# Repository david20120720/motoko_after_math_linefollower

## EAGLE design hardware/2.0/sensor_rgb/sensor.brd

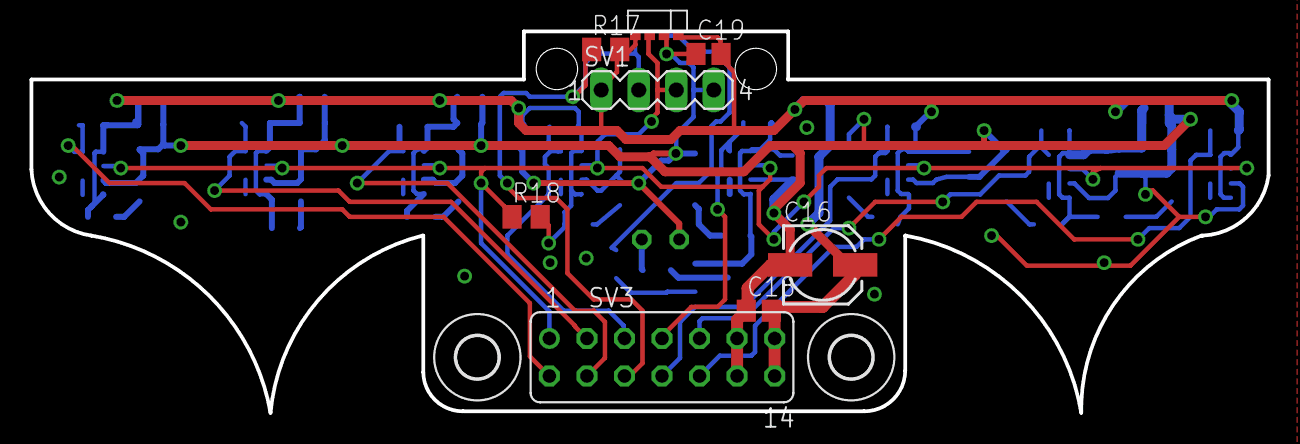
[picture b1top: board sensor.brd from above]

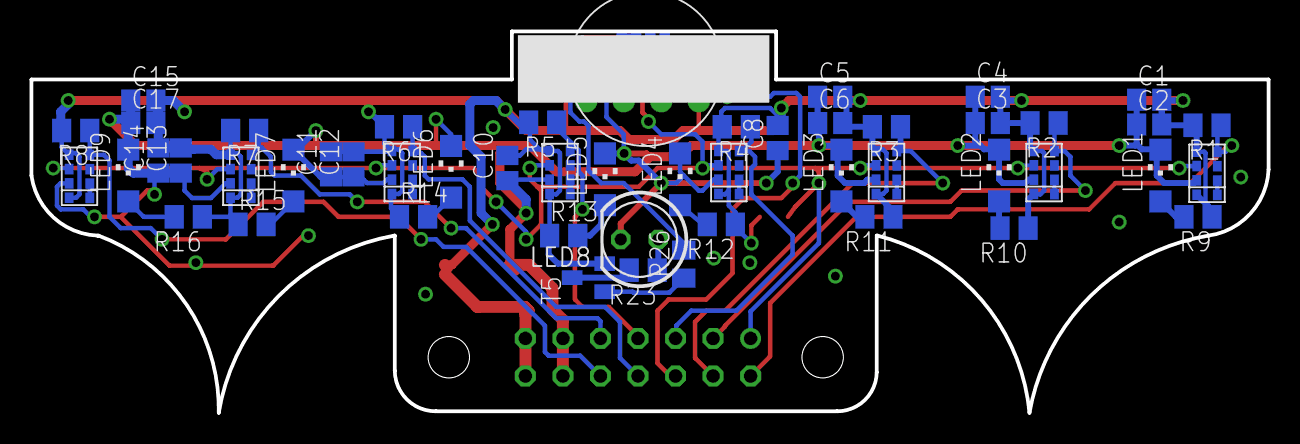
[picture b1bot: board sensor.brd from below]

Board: 2 copper layers, 83.7 x 25.8 mm, 61 parts (51 on the bottom side), 32 nets.

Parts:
C1, C3, C5, C11, C13, C15, C18: 10uF; C0805
C2, C4, C6, C8, C10, C12, C14, C17, C19: 100n; C0805
C16: 22uF; 153CLV-0505
H3, H4: MOUNT-HOLE2.8; 2,8
LED1, LED2, LED3, LED4, LED5, LED6, LED7, LED9: CHIPLED_1206
LED8: LED5MM
R1, R2, R3, R4, R5, R6, R7, R8, R17, R18: 4k7; M0805
R9, R10, R11, R12, R13, R14, R15, R16, R26: 330; M0805
R23: 22; M0805
SV1: MA04-1
SV3: FE07-2
T5: SOT23-BEC
U$1, U$4, U$5, U$6, U$7, U$8, U$9, U$10: APDS9950
U$2: APDS9950_EDGE
U$3: BALL_3/8

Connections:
+3V3: C1.2, C2.2, C3.2, C4.2, C5.2, C6.2, C8.2, C10.2, C11.2, C12.2, C13.2, C14.2, C15.2, C16.+, C17.2, C18.2, C19.2, R1.2, R2.2, R3.2, R4.2, R5.2, R6.2, R7.2, R8.2, R9.1, R10.1, R11.1, R12.1, R13.1, R14.1, R15.1, R16.1, R17.2, R18.2, SV1.1, SV3.13, SV3.14, T5.E, U$1.P$5, U$1.P$8, U$2.P$5, U$2.P$8, U$4.P$5, U$4.P$8, U$5.P$5, U$5.P$8, U$6.P$5, U$6.P$8, U$7.P$5, U$7.P$8, U$8.P$5, U$8.P$8, U$9.P$5, U$9.P$8, U$10.P$5, U$10.P$8
ADC0_: R8.1, SV3.10, U$10.P$1
ADC1_: R7.1, SV3.9, U$9.P$1
ADC2_: R6.1, SV3.8, U$8.P$1
ADC3_: R5.1, SV3.7, U$7.P$1
ADC4_: R4.1, SV3.5, U$6.P$1
ADC5_: R3.1, SV3.4, U$5.P$1
ADC6_: R2.1, SV3.3, U$4.P$1
ADC7_: R1.1, SV3.2, U$1.P$1
ADC8_: R17.1, SV1.2, SV3.6, U$2.P$1
GND: C1.1, C2.1, C3.1, C4.1, C5.1, C6.1, C8.1, C10.1, C11.1, C12.1, C13.1, C14.1, C15.1, C16.-, C17.1, C18.1, C19.1, LED1.C, LED2.C, LED3.C, LED4.C, LED5.C, LED6.C, LED7.C, LED8.K, LED9.C, SV1.4, SV3.11, SV3.12, U$1.P$6, U$2.P$6, U$4.P$6, U$5.P$6, U$6.P$6, U$7.P$6, U$8.P$6, U$9.P$6, U$10.P$6
unnamed: R23.2, T5.C
unnamed: U$4.P$3, U$4.P$4
unnamed: LED1.A, R9.2
unnamed: U$1.P$3, U$1.P$4
unnamed: LED2.A, R10.2
unnamed: LED3.A, R11.2
unnamed: LED4.A, R12.2
unnamed: LED5.A, R13.2
unnamed: U$5.P$3, U$5.P$4
unnamed: LED6.A, R14.2
unnamed: LED7.A, R15.2
unnamed: U$6.P$3, U$6.P$4
unnamed: LED9.A, R16.2
unnamed: R26.2, U$2.P$3, U$2.P$4
unnamed: U$7.P$3, U$7.P$4
unnamed: U$8.P$3, U$8.P$4
unnamed: U$9.P$3, U$9.P$4
unnamed: LED8.A, R23.1
unnamed: U$10.P$3, U$10.P$4
unnamed: R26.1, T5.B
SCL: R18.1, SV1.3, SV3.1, U$1.P$7, U$2.P$7, U$4.P$7, U$5.P$7, U$6.P$7, U$7.P$7, U$8.P$7, U$9.P$7, U$10.P$7

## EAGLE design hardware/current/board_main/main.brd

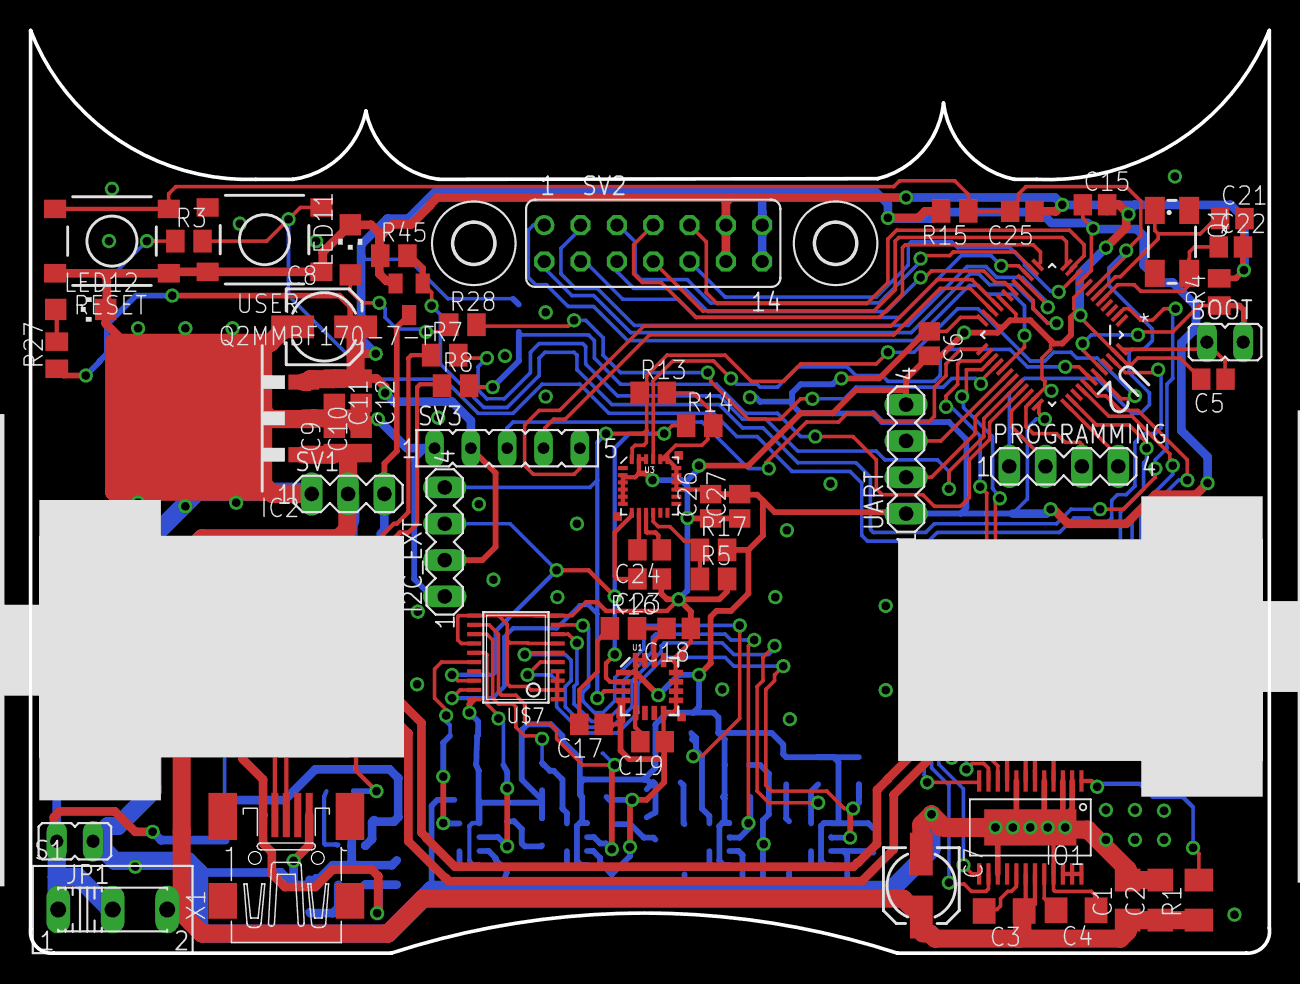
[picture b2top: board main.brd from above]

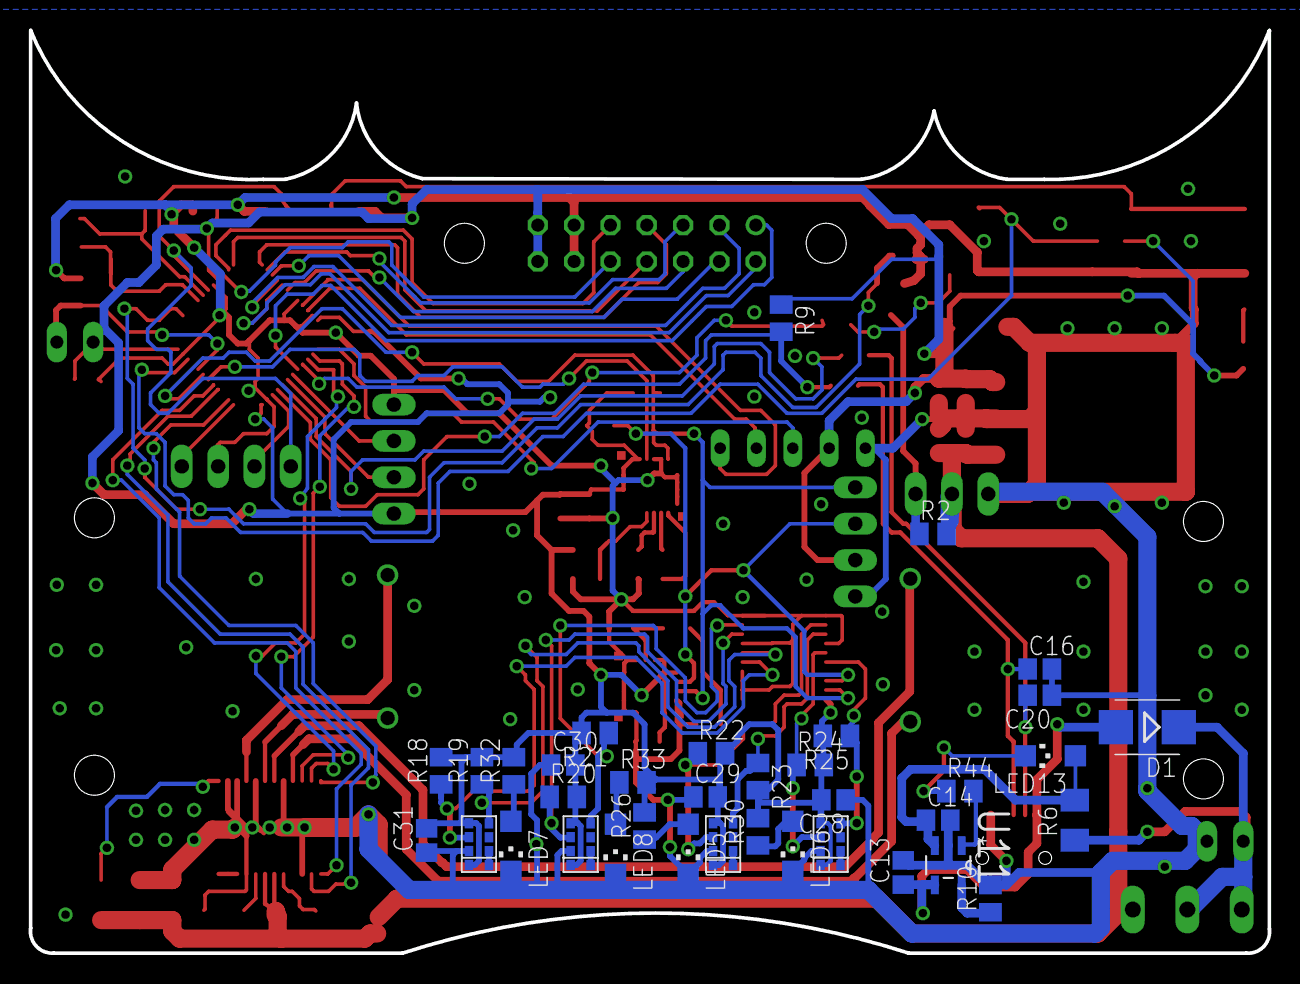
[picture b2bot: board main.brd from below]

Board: 2 copper layers, 86.6 x 64.5 mm, 99 parts (36 on the bottom side), 77 nets.

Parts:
BOOT: JP1
C1: 100n; C1206
C2: 10uF; C1206
C3: 10n; C1206
C4: 1uF; C1206
C5, C9, C11, C15, C19, C25, C26, C28, C29, C30, C31: 100n; C0805
C6, C10, C12, C13, C14, C27: 10uF; C0805
C7, C8: 22uF; 153CLV-0505
C16, C20: 22p; C0805
C17: 470n; C0805
C18: 10n; C0805
C21, C22: 18p; C0805
C23: 4.7uF; C0805
C24: 220n; C0805
D1: SMB
H1, H2: MOUNT-HOLE2.8; 2,8
I2C_EXT: MA04-1
IC2: LM2937; TO263-3
IO1: DRV8834; DRV8834_PCK
JP1: 2 or single CellLi-Pol; JP1
LED5, LED6, LED7, LED8, LED11: CHIPLED_1206
LED12: poweron; CHIPLED_1206
LED13: charging; CHIPLED_1206
PROGRAMMING: MA04-1
Q1: 8MHz; CTS406
Q2MMBF170-7-F: BSS123; SOT23
R1: 47k; M1206
R2, R3, R4, R5, R15, R17, R45: 47k; M0805
R6: 0R USE ONLY FOR SINGLE CELL; M1206
R7, R8: 22; M0805
R9: 1k5; M0805
R10, R16: 10k; M0805
R13, R14, R18, R19, R20, R21, R22, R23, R24, R25: 4k7; M0805
R26, R27, R28, R30, R32, R33, R44: 330; M0805
RESET: DTSM-6
S1: 255SB
SV1: SERVO/PWM; MA03-1
SV2: FE07-2
SV3: TSL1401 CAMERA; FE05-1
U1: L3G4200D; LGA16-4X4
U2: STM32F103C6T6A; QFP50P900X900X160-48N
U3: LSM9DS0; LGA-24
U11: MCP73831T-2DCI/OT; SOT95P270X145-5N
U$1, U$2: MICRO_METAL_GEAR_MOTOR
U$3, U$4, U$5, U$6: APDS9950
U$7: DSSCIRCUITS_PCA9544A; DSSCIRCUITS_TSSOP20
UART: MA04-1
USER: DTSM-6
X1: MINI-USB-32005-201; 32005-201

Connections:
+3V3: BOOT.1, C5.1, C6.1, C8.+, C11.1, C12.1, C15.1, C19.2, C26.2, C27.2, C28.2, C29.2, C30.2, C31.2, I2C_EXT.2, IC2.3, R3.1, R9.1, R13.2, R14.2, R15.2, R17.2, R18.2, R19.2, R20.2, R21.2, R22.2, R23.2, R24.2, R25.2, R26.2, R27.1, R30.2, R32.2, R33.2, SV2.13, SV2.14, SV3.2, U1.1, U1.5, U1.15, U1.16, U2.9, U2.24, U2.36, U2.48, U3.15, U3.16, U3.17, U3.18, U3.19, U3.20, U$3.P$5, U$3.P$8, U$4.P$5, U$4.P$8, U$5.P$5, U$5.P$8, U$6.P$5, U$6.P$8, U$7.20, UART.1
ADC0: SV2.10, U2.10
ADC1: SV2.9, U2.11
ADC2: SV2.8, U2.12
ADC3: SV2.7, U2.13
ADC4: SV2.5, U2.14
ADC5: SV2.4, U2.15
ADC6: SV2.3, U2.16
ADC7: SV2.2, U2.17
ADC8: SV2.6, U2.18
AENBL: IO1.10, U2.26
APHASE: IO1.13, U2.41
BATT: D1.C, JP1.2, R6.1, S1.1, S1.2
BENBL: IO1.11, U2.27
BPHASE: IO1.12, U2.38
CAM_AO: SV3.3, U2.25
CAM_CLK: SV3.4, U2.22
CAM_SI: SV3.5, U2.21
GND: C1.2, C2.2, C4.1, C5.2, C6.2, C7.-, C8.-, C9.2, C10.2, C11.2, C12.2, C13.2, C14.2, C15.2, C16.2, C17.1, C18.1, C19.1, C20.1, C21.2, C22.2, C23.1, C25.1, C26.1, C27.1, C28.1, C29.1, C30.1, C31.1, I2C_EXT.1, IC2.2, IO1.2, IO1.3, IO1.5, IO1.8, IO1.15, IO1.21, IO1.PAD, JP1.1, LED5.C, LED6.C, LED7.C, LED8.C, LED11.C, LED12.C, PROGRAMMING.3, Q2MMBF170-7-F.2, R4.2, R5.2, R10.2, R45.1, RESET.1, RESET.2, SV1.1, SV2.11, SV2.12, SV3.1, U1.4, U1.8, U1.9, U1.10, U1.11, U1.12, U1.13, U2.8, U2.20, U2.23, U2.35, U2.47, U3.2, U3.3, U3.4, U3.5, U3.6, U3.22, U3.23, U11.2, U$3.P$6, U$4.P$6, U$5.P$6, U$6.P$6, U$7.1, U$7.2, U$7.3, U$7.4, U$7.7, U$7.10, U$7.11, U$7.14, UART.4, USER.1, USER.2, X1.5
IR_CONTROLL: SV2.1, U2.29
LED_1: R28.2, U2.28
M1: IO1.14, U2.40
unnamed: IO1.4, U$1.P$1
unnamed: IO1.6, U$1.P$2
unnamed: IO1.9, U$2.P$1
unnamed: IO1.7, U$2.P$2
unnamed: C3.2, IO1.17
unnamed: C23.2, U3.7
unnamed: C24.2, U3.8
unnamed: IO1.22, IO1.23, IO1.24
unnamed: IO1.1, R1.2
unnamed: C24.1, U3.9
unnamed: BOOT.2, R4.1, U2.44
unnamed: R44.2, U11.1
unnamed: R5.1, R17.1, U3.10
unnamed: C18.2, R16.2, U1.14
unnamed: C17.2, R16.1
unnamed: U$6.P$3, U$6.P$4
unnamed: C4.2, IO1.20
unnamed: LED12.A, R27.2
unnamed: LED13.C, R44.1
unnamed: U$5.P$3, U$5.P$4
unnamed: Q2MMBF170-7-F.3, R2.1, SV1.3
unnamed: U$4.P$3, U$4.P$4
unnamed: U$3.P$3, U$3.P$4
unnamed: LED11.A, R28.1
unnamed: LED5.A, R26.1
unnamed: LED6.A, R30.1
unnamed: LED7.A, R32.1
unnamed: LED8.A, R33.1
unnamed: C14.1, LED13.A, R6.2, U11.3
unnamed: R10.1, U11.5
unnamed: C20.2, R7.1, X1.2
unnamed: C16.1, R8.1, X1.3
unnamed: C13.1, D1.A, U11.4, X1.1
OSCIN: C22.1, Q1.3, U2.5
OSCOUT: C21.1, Q1.1, U2.6
RESET: C25.2, PROGRAMMING.1, R15.1, RESET.3, RESET.4, U2.7
SCL: I2C_EXT.3, R14.1, U1.2, U2.42, U3.21, U$7.18
SCL0: R19.1, U$3.P$1, U$7.6
SCL1: R21.1, U$4.P$1, U$7.9
SCL2: R23.1, U$5.P$1, U$7.13
SCL3: R25.1, U$6.P$1, U$7.16
SDA: I2C_EXT.4, R13.1, U1.3, U2.43, U3.24, U$7.19
SDA0: R18.1, U$3.P$7, U$7.5
SDA1: R20.1, U$4.P$7, U$7.8
SDA2: R22.1, U$5.P$7, U$7.12
SDA3: R24.1, U$6.P$7, U$7.15
SERVO: Q2MMBF170-7-F.1, R45.2, U2.2
SWCLK: PROGRAMMING.4, U2.37
SWDIO: PROGRAMMING.2, U2.34
UART_RX: U2.31, UART.2
UART_TX: U2.30, UART.3
USBDM: R7.2, U2.32
USBDP: R8.2, R9.2, U2.33
USER_KEY_1: R3.2, U2.46, USER.3
VCC: C1.1, C2.1, C3.1, C7.+, C9.1, C10.1, IC2.1, IO1.18, IO1.19, R1.1, R2.2, S1.3, SV1.2
